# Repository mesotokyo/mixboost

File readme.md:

# MixBoost - Clean Booster & Loop Switcher & Send-Return mixer stompbox effector

## toggle mode by SW2

 * When SW2 is upper position, 'latch mode' - toggle ON/OFF by push SW1.
 * When SW2 is lower position, 'momentary mode' - ON while SW1 is pushed.

## toggle mode by SW3

 * When SW3 is lower position, 'booster mode'.
 * When SW3 is middle position, 'switch mode' - boosted signal is routed to 'send' and output is returned signal.
 * When SW3 is uppper position, 'mix mode' - boosted signal is routed to 'send', and output is returned signal mexed with input signal.

## jumper pins

 * Voltage source type can select by P1. +9V: uppper, +5V: lower (bypass 5V regulator).
 * When 'mix mode', mixed input signal can select by P2. non-boosted: lower, boosted: upper.

## component selectiong memo

 * recommend metal film resistor for R4, R5.
 * C4, C5, C15, C19 are non-polar electrolytic capacitors.
 * C6, C10 are electrolytic capacitors.
 * SW1 is momentary push switch - pay attention to orientation! pin 1 to left side.
 * SW2 is ON-ON toggle switch.
 * SW3 is ON-ON-ON toggle switch.
 * Q1, Q2 are 2N7000 MOSFET.
 * You can replace RV1 and RV2 to 10k.
 * D1 is BAT43.
 * recommend low noise OP-amp like 'NJM4580DD' for U2, 'NJM4580ND' for U4, U6.
 * You can replace U1 to R-78E5.
 * P3 is power inlet. GND is on right side.

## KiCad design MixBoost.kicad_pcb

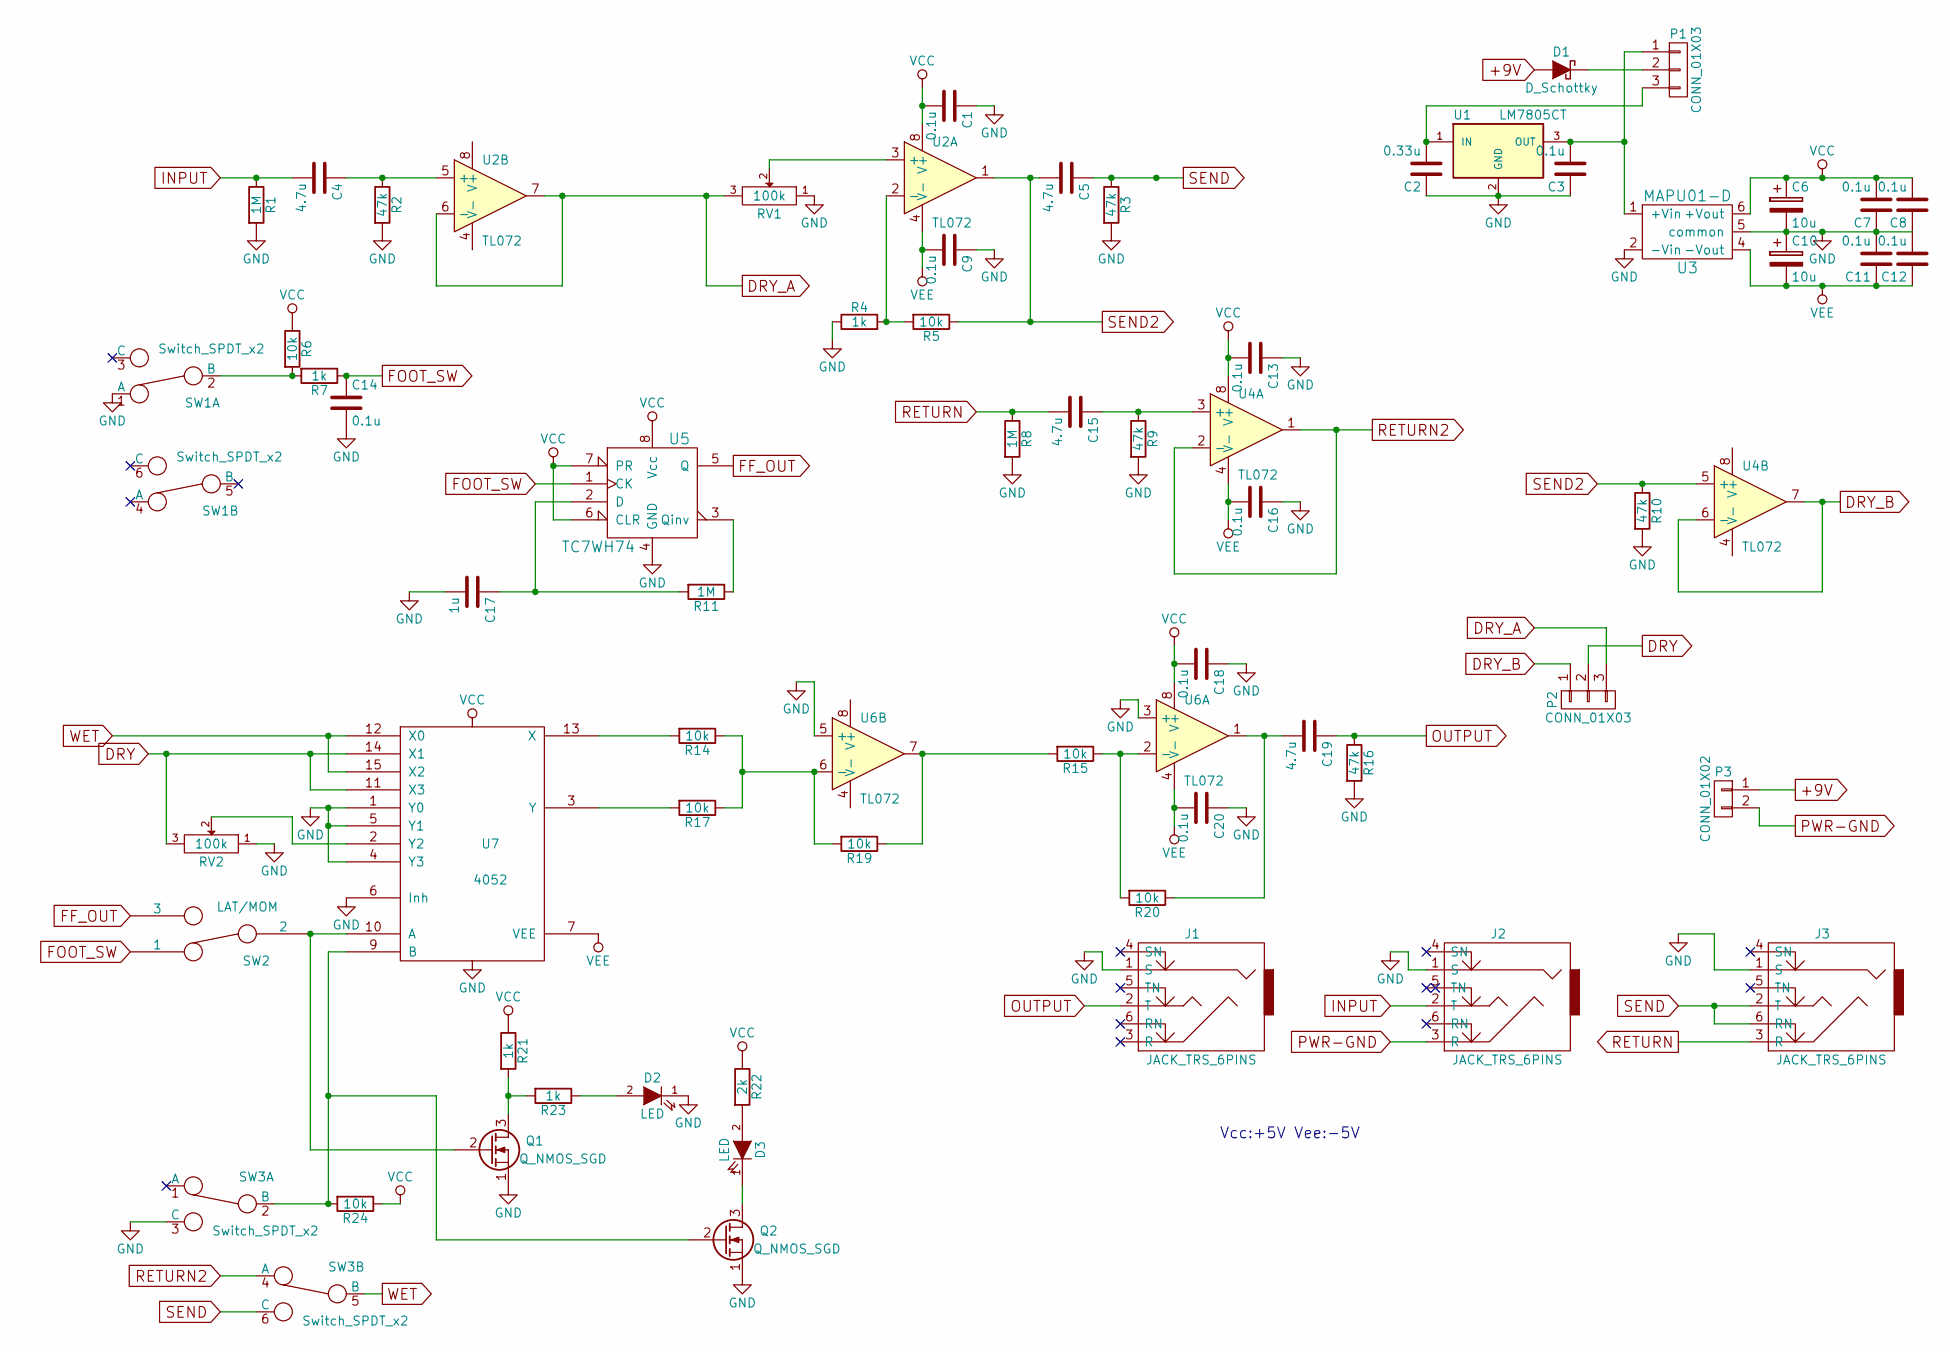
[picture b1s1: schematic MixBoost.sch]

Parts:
C1, C3, C7, C8, C9, C11, C12, C13, C14, C16, C18, C20: 0.1u; C_0805_HandSoldering
C2: 0.33u; C_0805_HandSoldering
C4, C5, C15, C19: 4.7u; CP_Radial_D5.0mm_P2.00mm
C6, C10: 10u; CP_Radial_D5.0mm_P2.00mm
C17: 1u; C_0805_HandSoldering
D1: D_Schottky; D_DO-41_SOD81_P7.62mm_Horizontal
D2: LED; LED_D5.0mm
D3: LED; LED_D3.0mm
J1, J2, J3: JACK_TRS_6PINS; NYS215
P1, P2: CONN_01X03; Pin_Header_Straight_1x03_Pitch2.54mm
P3: CONN_01X02; Pin_Header_Straight_1x02_Pitch2.54mm
Q1, Q2: Q_NMOS_SGD; TO-92_Molded_Narrow
R1, R8, R11: 1M; R_0805_HandSoldering
R2, R3, R9, R10, R16: 47k; R_0805_HandSoldering
R4, R7, R21, R23: 1k; R_0805_HandSoldering
R5, R6, R14, R15, R17, R19, R20, R24: 10k; R_0805_HandSoldering
R22: 2k; R_0805_HandSoldering
RV1: 100k; Potentiometer_WirePads
RV2: 100k; alpha_RV141F
SW1: Switch_SPDT_x2; alpha-push_DPDT
SW2: LAT/MOM; SPDT_switch
SW3: Switch_SPDT_x2; DPDT_switch
U1: LM7805CT; TO-220
U2: TL072; DIP-8_W7.62mm_Socket
U3: MAPU01-D; MAU100
U4, U6: TL072; DMP8
U5: TC7WH74; SSOP-8_2.95x2.8mm_Pitch0.65mm
U7: 4052; SOIC-16W_5.3x10.2mm_Pitch1.27mm

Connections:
+9V: D1.2 (A), P3.1
DRY: P2.2, RV2.3, U7.11 (X3), U7.14 (X1)
DRY_A: P2.3, RV1.3, U2.6 (-), U2.7
DRY_B: P2.1, U4.6 (-), U4.7
FF_OUT: SW2.3, U5.5 (Q)
FOOT_SW: C14.1, R7.1, SW2.1, U5.1 (CK)
GND: C1.1, C2.1, C3.1, C6.2, C7.1, C8.1, C9.1, C10.1, C11.2, C12.2, C13.1, C14.2, C16.1, C17.2, C18.1, C20.1, D2.1 (K), J1.1 (S), J2.1 (S), J3.1 (S), Q1.1 (S), Q2.1 (S), R1.2, R2.2, R3.2, R4.1, R8.2, R9.2, R10.2, R16.2, RV1.1, RV2.1, SW1.1 (A), SW3.3 (C), U1.2 (GND), U3.2 (-Vin), U3.5 (common), U5.4 (GND), U6.3 (+), U6.5 (+), U7.1 (Y0), U7.4 (Y3), U7.5 (Y1), U7.6 (Inh), U7.8 (VSS)
INPUT: C4.2, J2.2 (T), R1.1
unnamed: C2.2, P1.3, U1.1 (IN)
unnamed: C3.2, P1.1, U1.3 (OUT), U3.1 (+Vin)
unnamed: C4.1, R2.1, U2.5 (+)
unnamed: C15.1, R9.1, U4.3 (+)
unnamed: C17.1, R11.2, U5.2 (D)
unnamed: C19.2, R20.1, U6.1
unnamed: D1.1 (K), P1.2
unnamed: D2.2 (A), R23.1
unnamed: D3.1 (K), Q2.3 (D)
unnamed: D3.2 (A), R22.2
unnamed: Q1.2 (G), SW2.2, U7.10 (A)
unnamed: Q1.3 (D), R21.2, R23.2
unnamed: Q2.2 (G), R24.2, SW3.2 (B), U7.9 (B)
unnamed: R4.2, R5.2, U2.2 (-)
unnamed: R6.2, R7.2, SW1.2 (B)
unnamed: R11.1, U5.3 (Qinv)
unnamed: R14.1, R17.1, R19.2, U6.6 (-)
unnamed: R14.2, U7.13 (X)
unnamed: R15.1, R20.2, U6.2 (-)
unnamed: R15.2, R19.1, U6.7
unnamed: R17.2, U7.3 (Y)
unnamed: RV1.2, U2.3 (+)
unnamed: RV2.2, U7.2 (Y2)
OUTPUT: C19.1, J1.2 (T), R16.1
PWR-GND: J2.3 (R), P3.2
RETURN: C15.2, J3.3 (R), R8.1
RETURN2: SW3.4 (A), U4.1, U4.2 (-)
SEND: C5.1, J3.2 (T), J3.6 (RN), R3.1, SW3.6 (C)
SEND2: C5.2, R5.1, R10.1, U2.1, U4.5 (+)
VCC: C1.2, C6.1, C7.2, C8.2, C13.2, C18.2, R6.1, R21.1, R22.1, R24.1, U2.8 (V+), U3.6 (+Vout), U4.8 (V+), U5.6 (CLR), U5.7 (PR), U5.8 (Vcc), U6.8 (V+), U7.16 (VDD)
VEE: C9.2, C10.2, C11.1, C12.1, C16.2, C20.2, U2.4 (V-), U3.4 (-Vout), U4.4 (V-), U6.4 (V-), U7.7 (VEE)
WET: SW3.5 (B), U7.12 (X0), U7.15 (X2)

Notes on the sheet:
Vcc:+5V Vee:-5V

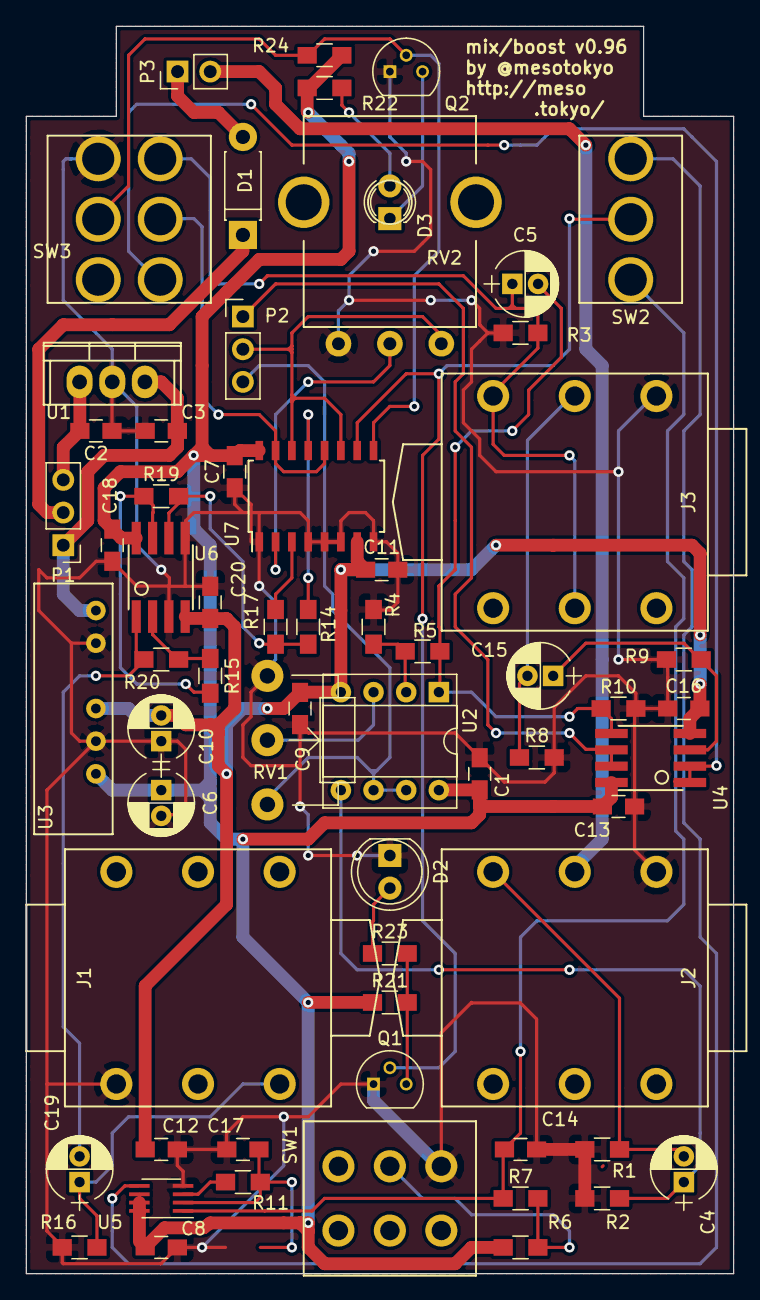
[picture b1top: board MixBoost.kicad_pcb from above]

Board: 2 copper layers, 55.0 x 97.0 mm, 64 parts (0 on the bottom side), 40 nets.

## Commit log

2017-09-04 add files
2017-09-04 bump version to 0.96

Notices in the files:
readme.md:
CC-BY-SA
